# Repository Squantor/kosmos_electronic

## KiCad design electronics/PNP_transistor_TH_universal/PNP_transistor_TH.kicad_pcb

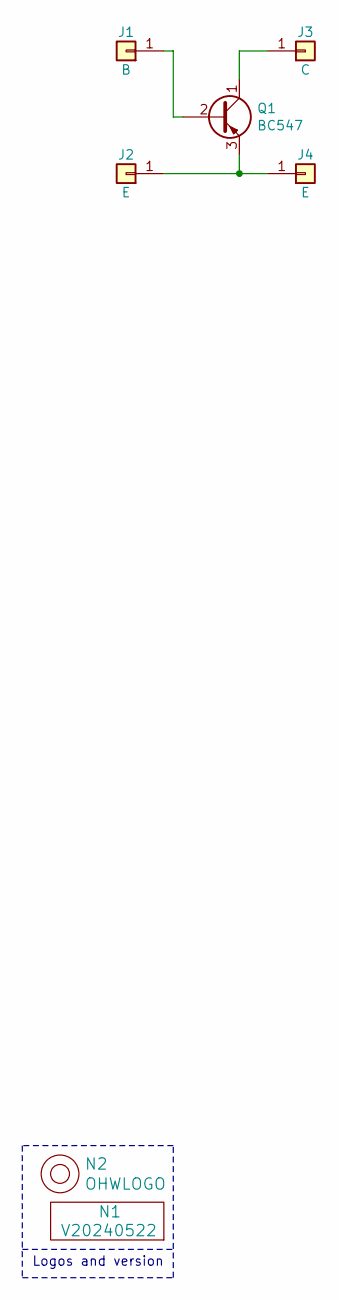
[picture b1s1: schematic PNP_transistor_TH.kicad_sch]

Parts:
J1: B; PC_pin_nail_head_6092
J2, J4: E; PC_pin_nail_head_6092
J3: C; PC_pin_nail_head_6092
N1: V20240522; Label_Generic
N2: OHWLOGO; OSHW-Symbol_6.7x6mm_SilkScreen
Q1: BC547; TO-92L_Inline_transistor_CBEBC

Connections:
unnamed: J1.1, Q1.2 (B)
unnamed: J2.1, J4.1, Q1.3 (E)
unnamed: J3.1, Q1.1 (C)

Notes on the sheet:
Logos and version

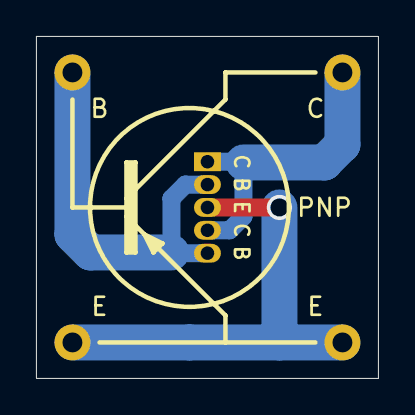
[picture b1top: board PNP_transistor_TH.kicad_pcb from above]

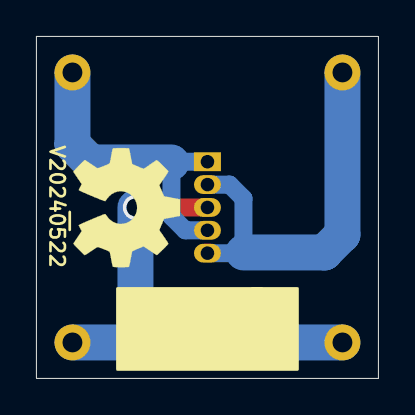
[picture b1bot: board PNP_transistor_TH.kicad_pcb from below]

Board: 2 copper layers, 19.0 x 19.0 mm, 7 parts (2 on the bottom side), 3 nets.

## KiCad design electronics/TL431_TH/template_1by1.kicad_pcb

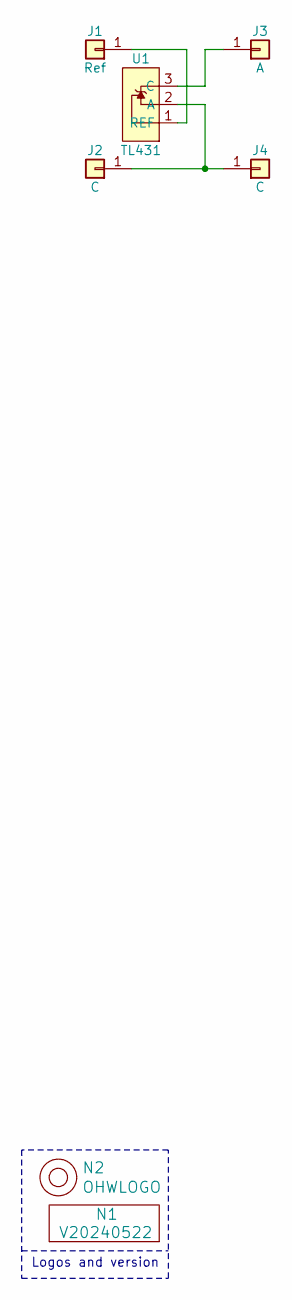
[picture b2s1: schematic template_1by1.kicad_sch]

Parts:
J1: Ref; PC_pin_nail_head_6092
J2, J4: C; PC_pin_nail_head_6092
J3: A; PC_pin_nail_head_6092
N1: V20240522; Label_Generic
N2: OHWLOGO; OSHW-Symbol_6.7x6mm_SilkScreen
U1: TL431; TO-92L_Inline

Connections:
unnamed: J1.1, U1.1 (REF)
unnamed: J2.1, J4.1, U1.2 (A)
unnamed: J3.1, U1.3 (C)

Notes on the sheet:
Logos and version

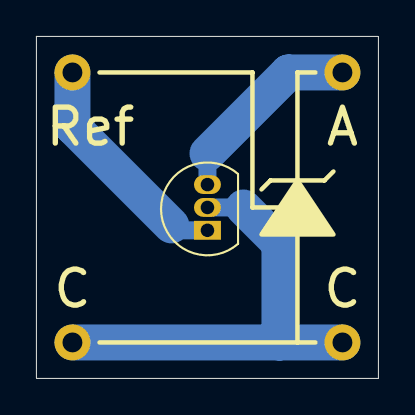
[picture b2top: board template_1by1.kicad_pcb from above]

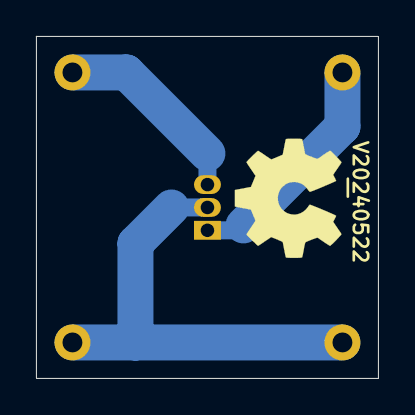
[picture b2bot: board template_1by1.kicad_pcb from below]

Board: 2 copper layers, 19.0 x 19.0 mm, 7 parts (2 on the bottom side), 3 nets.

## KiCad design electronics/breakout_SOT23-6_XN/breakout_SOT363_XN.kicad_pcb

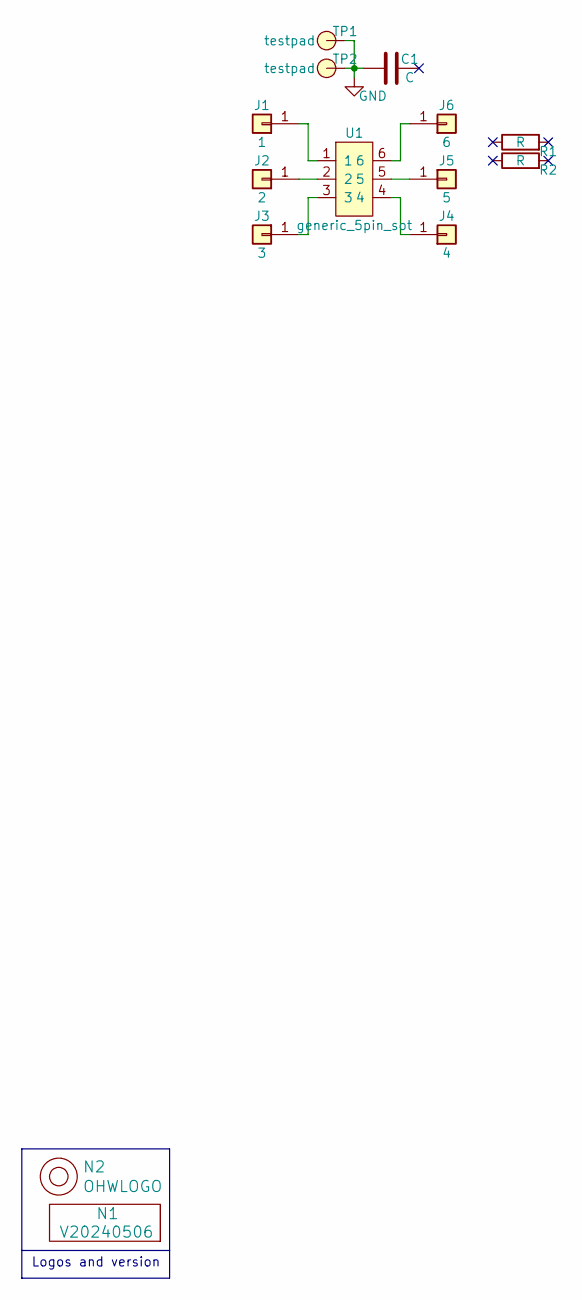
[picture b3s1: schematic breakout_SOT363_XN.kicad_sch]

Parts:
C1: C; C_0402+0603+0805+TH
J1: 1; PC_pin_nail_head_6092
J2: 2; PC_pin_nail_head_6092
J3: 3; PC_pin_nail_head_6092
J4: 4; PC_pin_nail_head_6092
J5: 5; PC_pin_nail_head_6092
J6: 6; PC_pin_nail_head_6092
N1: V20240506; Label_Generic
N2: OHWLOGO; OSHW-Symbol_6.7x6mm_SilkScreen
R1, R2: R; R_0805+0603
TP1, TP2: testpad; TestPoint_hole_H05R10_2side
U1: generic_5pin_sot; SOT363-NXP-hand

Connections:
GND: C1.1, TP1.1, TP2.1
unnamed: J1.1, U1.1
unnamed: J2.1, U1.2
unnamed: J3.1, U1.3
unnamed: J4.1, U1.4
unnamed: J5.1, U1.5
unnamed: J6.1, U1.6

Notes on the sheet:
Logos and version

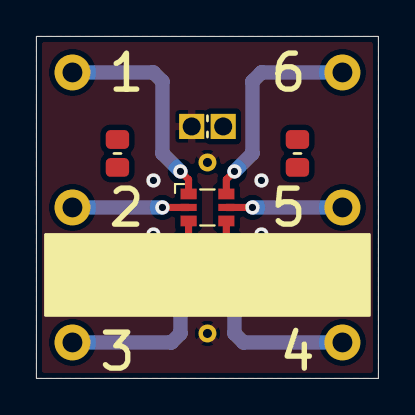
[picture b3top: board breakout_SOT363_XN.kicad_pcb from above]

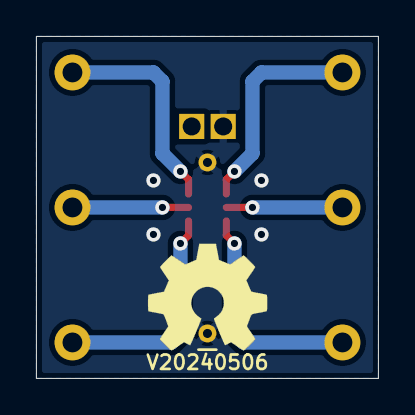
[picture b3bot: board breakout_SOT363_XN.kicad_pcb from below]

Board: 2 copper layers, 19.0 x 19.0 mm, 14 parts (2 on the bottom side), 7 nets.

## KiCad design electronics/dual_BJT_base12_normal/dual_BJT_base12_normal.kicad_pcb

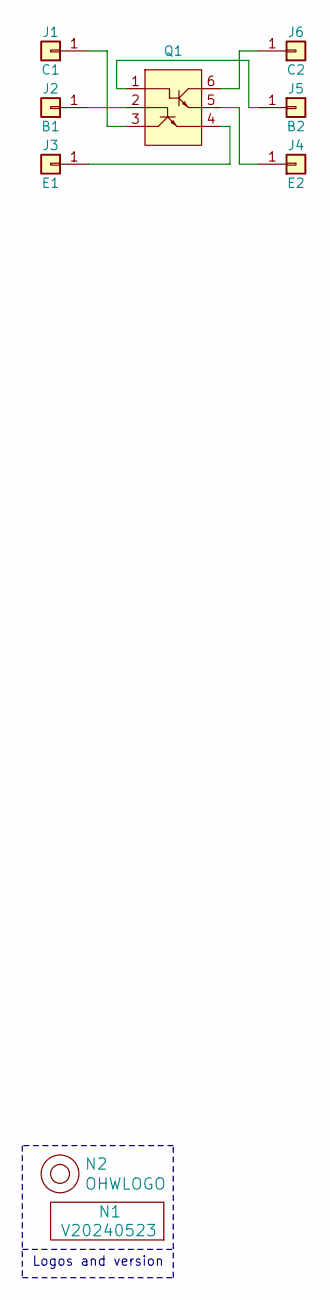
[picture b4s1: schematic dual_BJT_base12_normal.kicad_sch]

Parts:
J1: C1; PC_pin_nail_head_6092
J2: B1; PC_pin_nail_head_6092
J3: E1; PC_pin_nail_head_6092
J4: E2; PC_pin_nail_head_6092
J5: B2; PC_pin_nail_head_6092
J6: C2; PC_pin_nail_head_6092
N1: V20240523; Label_Generic
N2: OHWLOGO; OSHW-Symbol_6.7x6mm_SilkScreen
Q1: SOT363-NXP-hand

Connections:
unnamed: J1.1, Q1.3
unnamed: J2.1, Q1.2
unnamed: J3.1, Q1.4
unnamed: J4.1, Q1.5
unnamed: J5.1, Q1.1
unnamed: J6.1, Q1.6

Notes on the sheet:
Logos and version

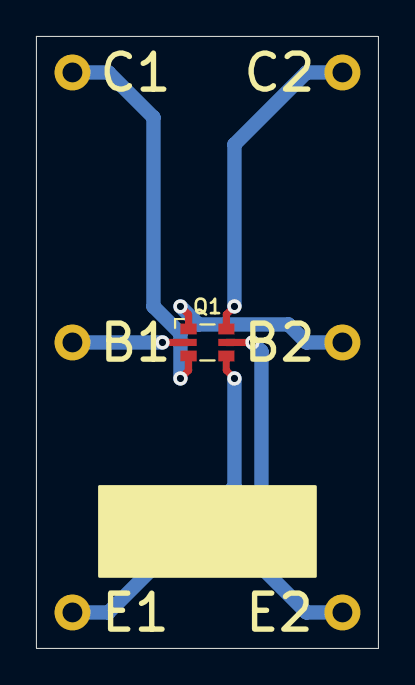
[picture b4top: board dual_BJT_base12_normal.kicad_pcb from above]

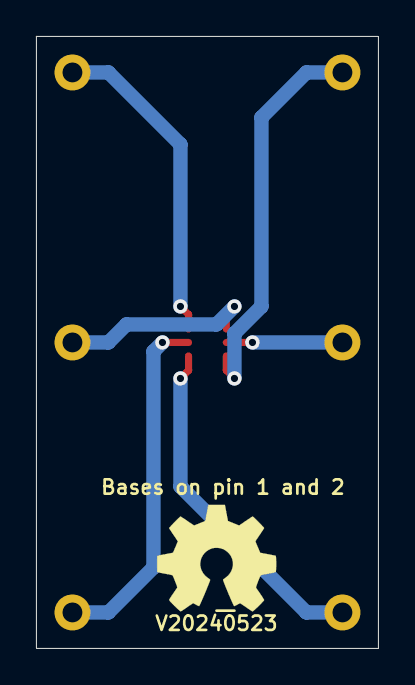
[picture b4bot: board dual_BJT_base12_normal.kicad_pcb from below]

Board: 2 copper layers, 19.0 x 34.0 mm, 9 parts (2 on the bottom side), 6 nets.

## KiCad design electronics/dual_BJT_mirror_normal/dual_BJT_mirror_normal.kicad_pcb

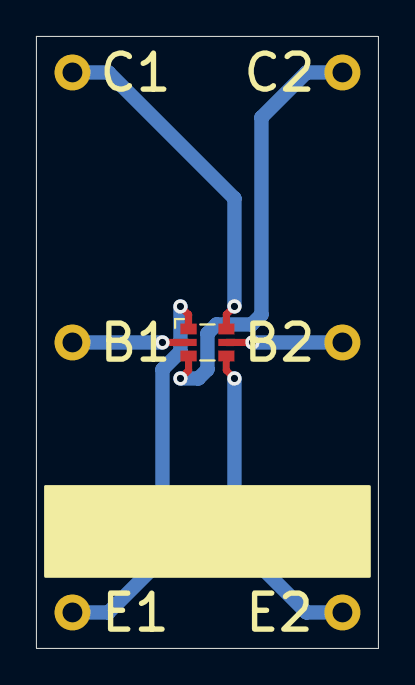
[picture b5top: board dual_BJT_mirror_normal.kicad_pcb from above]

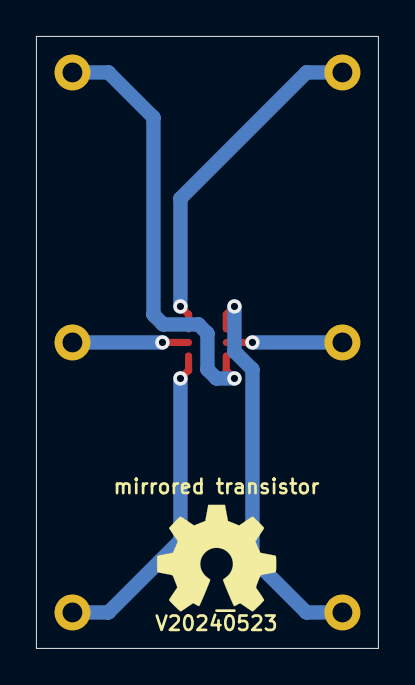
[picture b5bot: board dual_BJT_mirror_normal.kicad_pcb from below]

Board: 2 copper layers, 19.0 x 34.0 mm, 9 parts (2 on the bottom side), 6 nets.

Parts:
J1: C1; PC_pin_nail_head_6092
J2: B1; PC_pin_nail_head_6092
J3: E1; PC_pin_nail_head_6092
J4: E2; PC_pin_nail_head_6092
J5: B2; PC_pin_nail_head_6092
J6: C2; PC_pin_nail_head_6092
N1: V20240523; Label_Generic
N2: OHWLOGO; OSHW-Symbol_6.7x6mm_SilkScreen
Q1: SOT363-NXP-hand

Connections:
unnamed: J1.1, Q1.6
unnamed: J2.1, Q1.2
unnamed: J3.1, Q1.1
unnamed: J4.1, Q1.4
unnamed: J5.1, Q1.5
unnamed: J6.1, Q1.3
